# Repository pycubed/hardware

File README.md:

# Hardware ⚙
<br><br>
<br>

## [All PyCubed Resources](https://www.notion.so/maholli/All-PyCubed-Resources-8738cab0dd0743239a3cde30c6066452)
Tutorials, design resources, and more!
<br>

## Details:
- 4-layer PCB, minimum trace/spacing > 8 mils.
- Can be fabricated using standard FR4 for prototypes and Isola FR408HR for flight.
  - 50 ohm controlled impedance design spec'd for FR408HR with 11 mils external and 10.7 mils interal trace widths.
  - See [PyCubed's 2019 SmallSat Paper](https://github.com/pycubed/documentation/blob/master/PyCubed_smallsat-paper.pdf) for more discussion on the stack-up.
- Zipped, ready-to-order, gerber files can be found in the root of each revision directory. 
- NOTE: PyCubed layout has been ported from Eagle to KiCad to maintain the open-source nature of the project. Visit [http://www.kicad.org/](http://www.kicad.org/) for more details on this layout tool.
<br>

## Change Log
- [mainboard-v04 ➡ mainboard-v05](https://pycubed.org/v04-v05-Change-Log-7d80b1fb81be423a9da197f820e87538)
<br>

## Interactive Bill of Materials 🛒
- [mainboard-v01](https://pycubed.github.io/hardware/mainboard-v01)
- [mainboard-v02](https://pycubed.github.io/hardware/mainboard-v02)
- [mainboard-v04](https://pycubed.github.io/hardware/mainboard-v04)
- [mainboard-v05](https://pycubed.github.io/hardware/mainboard-v05)
<br>
<br>
<br>
<br>
<br>
<br>

## License
<br />
- Hardware in this repository is licensed under a <a rel="license" href="http://creativecommons.org/licenses/by-sa/4.0/">Creative Commons Attribution-ShareAlike 4.0 International License</a>.
- Software/firmware in this repository is licensed under MIT unless otherwise indicated.

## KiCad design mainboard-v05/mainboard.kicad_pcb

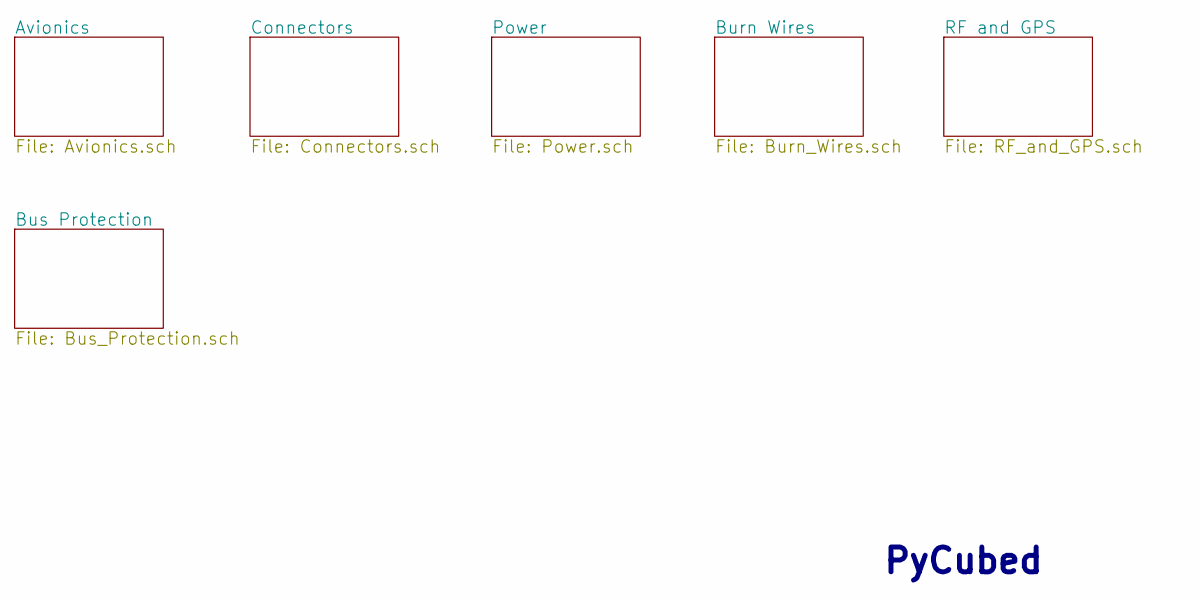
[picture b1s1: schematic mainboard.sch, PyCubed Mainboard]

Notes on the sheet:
PyCubed

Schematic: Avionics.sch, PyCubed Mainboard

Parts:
C1, C2: 8pF; C_0603_1608Metric
C3, C5, C7, C9, C10, C11: 0.1uF; C_0603_1608Metric
C4, C12, C13, C15: 1uF; C_0603_1608Metric
C14, C16: 10uF; C_0603_1608Metric
D1: WS2812B; LED_WS2812B_PLCC4_5.0x5.0mm_P3.2mm; Manufacturer_Part_Number WS2812B-B
H1, H2, H3, H4: MountingHole_Pad; MountingHole_3.2mm_M3_DIN965_Pad
J8: Conn_01x09; PinHeader_1x09_P2.54mm_Vertical
J9: Conn_01x03; PinHeader_1x03_P2.54mm_Vertical
J10: Conn_01x04; PinHeader_1x04_P2.54mm_Vertical
J15: Conn_01x02; PinHeader_CUSTOM3
L1: 10uH; L_0805_2012Metric_Pad1.15x1.40mm_HandSolder; Manufacturer_Part_Number MGFL2012F100MT-LF
R1: 316K; R_0603_1608Metric
R2: 110K; R_0603_1608Metric
R3, R4, R44, R45: 10K; R_0603_1608Metric
R6: 4.7k; R_0603_1608Metric
R7, R41, R42: 10k; R_0603_1608Metric
SW1: KMR231NG LFS; BTN_KMR2_4.6X2.8; Manufacturer_Part_Number KMR231NG LFS
U1: MAX706RESA; SO-8_3.9x4.9mm_P1.27mm; Manufacturer_Part_Number MAX706RESA
U2: ATSAMD51J19A-AU; QFP50P1200X1200X120-64N; Manufacturer_Part_Number ATSAMD51J19A-AU
U3: BMX160; Manufacturer_Part_Number BMX160
Y1: 32.768kHz; Crystal_SMD_3215-2Pin_3.2x1.5mm; Manufacturer_Part_Number SC-32S32.768kHz20PPM7pF

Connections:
3.3V: C5.1, C7.1, C9.2, C10.1, C11.1, C13.1, C15.1, C16.1, D1.1 (VDD), J8.1, J10.4, R3.1, R4.1, R44.1, R45.1, U1.2, U2.4 (PA03), U2.8 (VDDANA), U2.21 (VDDIO), U2.34 (VDDIO1), U2.48 (VDDIO2), U2.56 (VDDIO3), U3.5, U3.8, U3.12; also elsewhere on the board
/Avionics/BATTERY: C3.1, R1.2, R2.2, U2.15 (PA06)
/Avionics/XTAL1: C1.1, U2.1 (PA00), Y1.1
/Avionics/XTAL2: C2.1, U2.2 (PA01), Y1.2
AIN5: J10.2, U2.14 (PA05)
BURN_RELAY_A: U2.28 (PB15); also elsewhere on the board
DAC0: J10.1, U2.3 (PA02)
ENAB_BURN1: U2.60 (PB31); also elsewhere on the board
ENAB_BURN2: U2.32 (PA15); also elsewhere on the board
ENAB_GPS: U2.62 (PB01); also elsewhere on the board
ENAB_RF: U2.13 (PA04); also elsewhere on the board
FLASH_CS: U2.24 (PB11); also elsewhere on the board
FLASH_IO2: U2.19 (PA10); also elsewhere on the board
FLASH_IO3: U2.20 (PA11); also elsewhere on the board
FLASH_MISO: U2.18 (PA09); also elsewhere on the board
FLASH_MOSI: U2.17 (PA08); also elsewhere on the board
FLASH_SCK: U2.23 (PB10); also elsewhere on the board
GND: C1.2, C2.2, C3.2, C4.1, C5.2, C7.2, C9.1, C10.2, C11.2, C12.1, C13.2, C14.2, C15.2, C16.2, D1.3 (VSS), H1.1, H2.1, H3.1, H4.1, J8.2, J10.3, R2.1, R7.1, R41.2, SW1.B (S), SW1.B' (S1), U1.3, U1.4, U2.7 (GND), U2.22 (GND1), U2.33 (GND2), U2.47 (GND3), U2.54 (GND4), U3.2, U3.3, U3.6, U3.7; also elsewhere on the board
L1_PROG: R6.1; also elsewhere on the board
MISO: J8.5, U2.31 (PA14); also elsewhere on the board
MOSI: J8.3, U2.29 (PA12); also elsewhere on the board
unnamed: C12.2, C14.1, L1.1, U2.53 (VDDCORE)
unnamed: D1.4 (DIN), U2.42 (PA21)
unnamed: L1.2, U2.55 (VSW)
unnamed: R6.2, U2.16 (PA07)
unnamed: R41.1, U3.1
unnamed: R42.2, U1.7
unnamed: U1.1, U1.8
PA16: J15.2, U2.35 (PA16); also elsewhere on the board
PA17: J15.1, U2.36 (PA17); also elsewhere on the board
PA19: J9.3, U2.38 (PA19); also elsewhere on the board
PA20: J8.8, U2.41 (PA20); also elsewhere on the board
PA22: J8.9, U2.43 (PA22); also elsewhere on the board
PB16: J9.2, U2.39 (PB16); also elsewhere on the board
PB17: J9.1, U2.40 (PB17); also elsewhere on the board
PB22: J8.7, U2.49 (PB22); also elsewhere on the board
PB23: J8.6, U2.50 (PB23); also elsewhere on the board
RF1_CS: U2.59 (PB30); also elsewhere on the board
RF1_IO0: U2.6 (PB05); also elsewhere on the board
RF1_IO4: U2.5 (PB04); also elsewhere on the board
RF1_RST: U2.61 (PB00); also elsewhere on the board
RF2_CS: U2.12 (PB09); also elsewhere on the board
RF2_IO0: U2.9 (PB06); also elsewhere on the board
RF2_IO4: U2.10 (PB07); also elsewhere on the board
RF2_RST: U2.27 (PB14); also elsewhere on the board
RX: U2.64 (PB03); also elsewhere on the board
SCK: J8.4, U2.30 (PA13); also elsewhere on the board
SCL: R45.2, U2.26 (PB13); also elsewhere on the board
SCL_IMU: U3.13; also elsewhere on the board
SDA: R44.2, U2.25 (PB12); also elsewhere on the board
SDA_IMU: U3.14; also elsewhere on the board
SD_CS: U2.51 (PA27); also elsewhere on the board
SWCLK: R4.2, U2.57 (PA30); also elsewhere on the board
SWDIO: U2.58 (PA31); also elsewhere on the board
TX: U2.63 (PB02); also elsewhere on the board
USB_D+: U2.46 (PA25); also elsewhere on the board
USB_D-: U2.45 (PA24); also elsewhere on the board
VBATT: R1.1; also elsewhere on the board
VBUS_RESET: U2.37 (PA18); also elsewhere on the board
WDT_WDI: R7.2, U1.6, U2.44 (PA23)
~CHRG: U2.11 (PB08); also elsewhere on the board
~RESET: C4.2, R3.2, R42.1, SW1.A, SW1.A' (P1), U2.52 (RESETN); also elsewhere on the board

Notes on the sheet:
IMU
External Watch-Dog Timer
DECOUPLING
JTAG
RESET
PRIMARY PROCESSOR
Breakout Pins
Mounting Holes
Avionics
I2C ADDR
0x68
WDT enabled when installed
TCK TMS
NOTE: Components labeled "do not install" (DNI) are not populated by default
PCC D[0]-D[8]
SCL2
SDA2

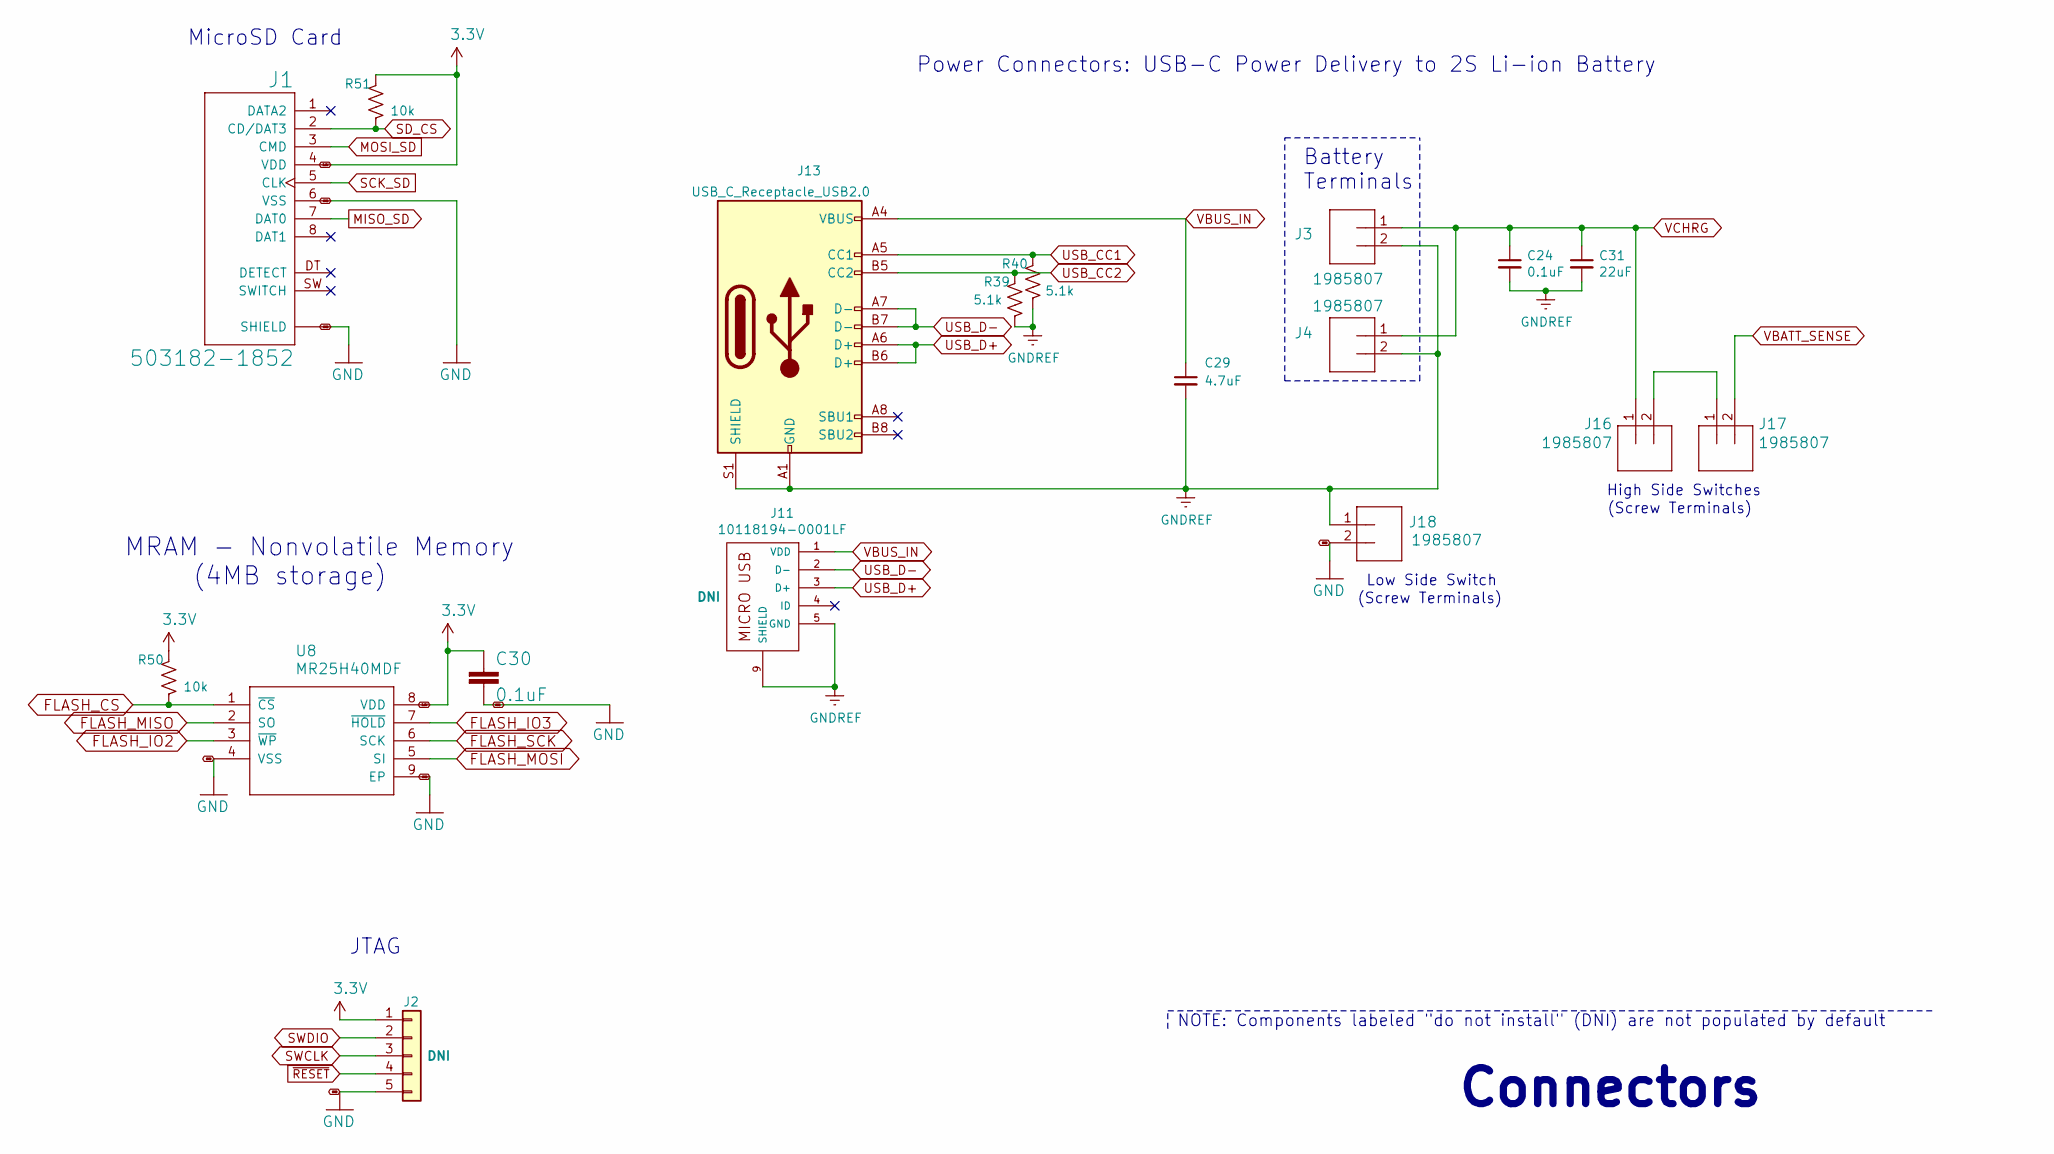
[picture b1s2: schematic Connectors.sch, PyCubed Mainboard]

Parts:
C24, C30: 0.1uF; C_0603_1608Metric
C29: 4.7uF; C_0603_1608Metric
C31: 22uF; C_0603_1608Metric
J1: 503182-1852; MOLEX_503182-1852; Manufacturer_Part_Number 5031821852
J2: Conn_01x05; PinHeader_1x05_P2.54mm_Vertical
J3, J4, J16, J17, J18: 1985807; SCREWTERMINAL-3.5MM-2_LOCK; Manufacturer_Part_Number 1985807
J11: 10118194-0001LF
J13: USB_C_Receptacle_USB2.0; USB_C_Receptacle_XKB_U262-161N-4BVC11; Manufacturer_Part_Number U262-161N-4BVC11
R39, R40: 5.1k; R_0603_1608Metric
R50, R51: 10k; R_0603_1608Metric
U8: MR25H40MDF; SON127P600X500X90-9N; Manufacturer_Part_Number W25Q80DVSNIG

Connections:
3.3V: C30.1, J1.4 (VDD), J2.1, R50.2, R51.2, U8.8 (VDD); also elsewhere on the board
FLASH_CS: R50.1, U8.1 (~CS); also elsewhere on the board
FLASH_IO2: U8.3 (~WP); also elsewhere on the board
FLASH_IO3: U8.7 (~HOLD); also elsewhere on the board
FLASH_MISO: U8.2 (SO); also elsewhere on the board
FLASH_MOSI: U8.5 (SI); also elsewhere on the board
FLASH_SCK: U8.6 (SCK); also elsewhere on the board
GND: C30.2, J1.6 (VSS), J1.P1 (SHIELD), J1.P2 (SHIELD), J1.P3 (SHIELD), J1.P4 (SHIELD), J1.P5 (SHIELD), J2.5, J18.2, U8.4 (VSS), U8.9 (EP); also elsewhere on the board
GNDREF: C24.2, C29.2, C31.2, J3.2, J4.2, J11.5 (GND), J11.8, J11.9 (SHIELD), J13.A1 (GND), J13.A12 (GND), J13.B1 (GND), J13.B12 (GND), J13.S1 (SHIELD), J18.1, R39.1, R40.1; also elsewhere on the board
MISO_SD: J1.7 (DAT0); also elsewhere on the board
MOSI_SD: J1.3 (CMD); also elsewhere on the board
unnamed: J16.2, J17.1
SCK_SD: J1.5 (CLK); also elsewhere on the board
SD_CS: J1.2 (CD/DAT3), R51.1; also elsewhere on the board
SWCLK: J2.3; also elsewhere on the board
SWDIO: J2.2; also elsewhere on the board
USB_CC1: J13.A5 (CC1), R40.2
USB_CC2: J13.B5 (CC2), R39.2
USB_D+: J11.3 (D+), J13.A6 (D+), J13.B6 (D+); also elsewhere on the board
USB_D-: J11.2 (D-), J13.A7 (D-), J13.B7 (D-); also elsewhere on the board
VBATT_SENSE: J17.2; also elsewhere on the board
VBUS_IN: C29.1, J11.1 (VDD), J13.A4 (VBUS), J13.A9 (VBUS), J13.B4 (VBUS), J13.B9 (VBUS); also elsewhere on the board
VCHRG: C24.1, C31.1, J3.1, J4.1, J16.1; also elsewhere on the board
~RESET: J2.4; also elsewhere on the board

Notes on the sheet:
High Side Switches
Battery Terminals
JTAG
Power Connectors: USB-C Power Delivery to 2S Li-ion Battery
MicroSD Card
MRAM - Nonvolatile Memory (4MB storage)
Connectors
Low Side Switch
NOTE: Components labeled "do not install" (DNI) are not populated by default
(Screw Terminals)

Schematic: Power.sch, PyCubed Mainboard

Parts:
C6, C22, C35, C39, C43: 10uF; C_0603_1608Metric
C17, C18, C28, C37, C38: 22uF; C_0603_1608Metric
C19, C20: 100uF; C_1210_3225Metric
C21, C45: 0.1uF; C_0603_1608Metric
C23: 2.2uF; C_0603_1608Metric
C25: 22nF; C_0603_1608Metric
C26, C32: 3.3nF; C_0603_1608Metric
C27, C33: 1uF; C_0603_1608Metric
C34: 4.7uF; C_0603_1608Metric
C36: 47nF; C_0603_1608Metric
D2: DFLS130L; PWRDI-123; Manufacturer_Part_Number DFLS130L-7
D5: GREEN LED; LED_0603_1608Metric; Manufacturer_Part_Number LTST-C190KGKT
J14: Conn_01x06; PinHeader_1x06_P2.54mm_Vertical
JP6, JP7: Jumper_3_Bridged12; SolderJumper-3_P1.3mm_Bridged12_RoundedPad1.0x1.5mm
L2: 3.3uH; L_2141; Manufacturer_Part_Number HPC5040NF-3R3MTH
L3: 33uH; L_1812_4532Metric; Manufacturer_Part_Number SNR5040K-330M
L4: 1uH; L_2510; Manufacturer_Part_Number MCS25GD-1R0MMP
Q1: IRLML2803; SOT-23; Manufacturer_Part_Number IRLML2803TRPbF
Q2, Q3: MBT2222ADW1T1; SOT-363_SC-70-6; Manufacturer_Part_Number MBT2222ADW1T1G
Q22: NDS8434; Manufacturer_Part_Number NDS8434
R8: 0.1; R_2512_6332Metric
R9: 107K; R_0603_1608Metric
R10: 0; R_0603_1608Metric
R11: 787K; R_0603_1608Metric
R12: 121K; R_0603_1608Metric
R13, R29: 73.2K; R_0603_1608Metric
R14: 22.1K; R_0603_1608Metric
R15, R30, R49: 100K; R_0603_1608Metric
R16: 845K; R_0603_1608Metric
R17, R18: 100k; R_0603_1608Metric
R19: 2.1M; R_0603_1608Metric
R20: 3.01K; R_0603_1608Metric
R21, R31, R46, R52, R55: 10K; R_0603_1608Metric
R22: 4.7K; R_0603_1608Metric
R23, R59: 3.3K; R_0603_1608Metric
R26: 1K; R_0603_1608Metric
R34: 5.23K; R_0603_1608Metric
R35: 30.1K; R_0603_1608Metric
R36: 3.16K; R_0603_1608Metric
R47: 200K; R_0603_1608Metric
R110: 20K; R_0603_1608Metric
U4: ADM1176-1ARMZ-R7; Manufacturer_Part_Number ADM1176-1ARMZ-R7
U5: TPS54226PWPRPWP14_2P31X2P46-L; PWP14_2P31X2P46-L; Manufacturer_Part_Number TPS54226PWPR
U6: LTC4121; QFN-16-PAD; Manufacturer_Part_Number LTC4121EUD
U7: KF50BD-TR; SOIC127P600X175-8N; Manufacturer_Part_Number KF50BD-TR
U17: BQ25883RGER; QFN50P400X400X100-25N-D; Manufacturer_Part_Number BQ25883RGER
U21: TPS7A4501DCQT; Manufacturer_Part_Number TPS7A4501DCQT

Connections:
3.3V: C17.2, C18.2, JP6.3 (B), JP7.3 (B), L2.2, Q22.1, Q22.2, Q22.3, R13.2, R17.2, R18.2, R23.1, U5.1 (VO); also elsewhere on the board
/Power/3V3_EN: Q2.6 (C1), R29.2, U5.7 (EN)
/Power/REGN: C34.1, R31.2, U17.11
/Power/VCHRG_IN: C22.1, D2.C, R10.2, R11.2, U6.P$3
/Power/V_RF: C43.2, JP6.1 (A), JP7.1 (A), R55.1, U7.1, U21.4
ENAB_GPS: R21.1, R22.1; also elsewhere on the board
ENAB_RF: U7.5, U21.1; also elsewhere on the board
GND: C17.1, C18.1, C19.2, C20.2, C22.2, C23.2, C26.2, C27.2, C28.2, C32.1, C43.1, C45.1, J14.5, Q1.2 (S), Q2.1 (E1), Q2.4 (E2), Q3.1 (E1), Q3.4 (E2), R9.2, R12.1, R14.1, R20.1, R21.2, R59.2, U4.4, U5.5 (GND), U5.8 (PGND1), U5.9 (PGND2), U5.15 (EPAD), U6.P$5, U6.P$7, U6.P$12, U6.P$17, U7.2, U7.3, U7.6, U7.7, U21.3, U21.6; also elsewhere on the board
GNDREF: C33.1, C34.2, C35.1, C37.1, C38.1, C39.1, J14.6, R35.1, R36.1, R46.1, U17.19, U17.20, U17.25; also elsewhere on the board
GPS_PWR_IN: Q22.5, Q22.6, Q22.7, Q22.8; also elsewhere on the board
L1_PROG: R20.2, U6.P$13; also elsewhere on the board
unnamed: C6.1, Q3.3 (C2), Q3.6 (C1), R49.2
unnamed: C6.2, Q2.5 (B2), R47.2
unnamed: C21.1, L2.1, U5.10 (SW1), U5.11 (SW2)
unnamed: C21.2, U5.12 (VBST)
unnamed: C23.1, U6.P$1
unnamed: C25.1, U6.P$2
unnamed: C25.2, L3.2, U6.P$4
unnamed: C26.1, U5.4 (SS)
unnamed: C27.1, R15.2, U5.3 (VREG5)
unnamed: C32.2, U4.5
unnamed: C35.2, L4.1, U17.21, U17.22
unnamed: C36.1, L4.2, U17.17, U17.18
unnamed: C36.2, U17.12
unnamed: C37.2, C38.2, J14.1, U17.15, U17.16
unnamed: C39.2, J14.3, U17.13, U17.14
unnamed: D5.2 (A), R31.1
unnamed: L3.1, U6.P$8
unnamed: Q1.1 (G), R22.2
unnamed: Q1.3 (D), Q22.4, R23.2
unnamed: Q2.2 (B1), Q2.3 (C2), R30.2, R110.2
unnamed: Q3.2 (B1), R110.1
unnamed: Q3.5 (B2), R52.1
unnamed: R9.1, R10.1, U6.P$16
unnamed: R11.1, R12.2, U6.P$6
unnamed: R13.1, R14.2, U5.2 (VFB)
unnamed: R15.1, U5.6 (PG)
unnamed: R16.1, U6.P$11
unnamed: R16.2, R19.2, U6.P$10
unnamed: R18.1, U6.P$15
unnamed: R26.2, U4.3
unnamed: R36.2, U17.8
unnamed: R55.2, R59.1, U21.5
SCL_PWR: U4.6, U17.5; also elsewhere on the board
SDA_PWR: U4.7, U17.4; also elsewhere on the board
STAT: D5.1 (K), U17.2
THM: R34.2, R35.2, R46.2, U17.7
USB_D+: U17.24; also elsewhere on the board
USB_D-: U17.1; also elsewhere on the board
VBATT: C19.1, C20.1, C28.1, C45.2, J14.2, R8.1, R19.1, R26.1, R29.1, R30.1, R47.1, R49.1, U4.2, U5.13 (VIN), U5.14 (VCC), U6.P$9, U7.8, U21.2; also elsewhere on the board
VBATT_SENSE: R8.2, U4.1; also elsewhere on the board
VBUS_IN: C33.2, R34.1, U17.23; also elsewhere on the board
VBUS_RESET: R52.2; also elsewhere on the board
VCC_RF1: JP6.2 (C); also elsewhere on the board
VCC_RF2: JP7.2 (C); also elsewhere on the board
VCHRG: J14.4; also elsewhere on the board
VSOLAR: D2.A; also elsewhere on the board
~CHRG: R17.1, U6.P$14; also elsewhere on the board

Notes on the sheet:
GPS Power
Regulator - 3.3V OUT
VBATT 4.5 to 18V
L1_PROG monitors charge current using: Ichrg=988*Vprog/Rprog 3.01K = 400mA max charge current
USB (Boost) Charging for 2-cell Li-Ion
Addr: 0x94
Power
Populating R9=107K,R10=464K sets turn-on voltage to 12V (solar input). Use this to tune efficiency
Vfloat=8.4V (2S Li-ion)
"VUSB"
VSOLAR 9V to 40V
Current Sense Resistor: 1.0 Ohm is about 0.3mW power lost as heat
NOTE: Components labeled "do not install" (DNI) are not populated by default
Input Current Limit Max input current (IINMAX)=KILIM/RILIM KILIM = 1098 to 1276 at most IINMAX=400mA=3.16 kohm
Sets EN low dwell time
"One Shot" Regulator Reset
Battery Power Monitor
"VCHRG"
"GND"
RBF Jumpers
Add jumper to allow USB battery charging (even inside P-Pod).
Add jumper to allow USB to power the board (even inside P-Pod).
Remove both jumpers before flight to remove risk of unknown BQ25883 radiation failure modes
MPPT=75% Voc R11=787K, R12=121K To disable MPTT: R11=10k; R12=DNI
MPPT on by default
2S Li-Ion Battery Solar Charging Circuit
RF Regulator
Radio VDD Select
Set RF Voltage: VOUT=1.21*(1+R55/R59)+(3E-6*R55) VOUT=5V (R55=10K, R59=3.3K)
Alternative RF Regulator B/C of 2021 Chip Shortage
LOW = enabled Opposite polarity than other RF reg..
Value is convenient, not necessary. 10K-80K would also work for R29

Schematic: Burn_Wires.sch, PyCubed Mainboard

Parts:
D4: DFLS130L; PWRDI-123; Manufacturer_Part_Number DFLS130L-7
JP8, JP9, JP10, JP11, JP12, JP13, JP14, JP15: Conn_01x03; MOLEX-1X3_LOCK; Manufacturer_Part_Number 22-23-2037
Q4: IRLML2803; SOT-23; Manufacturer_Part_Number IRLML2803TRPbF
Q5: IRLML2803; SOT-23; Manufacturer_Part_Number MMBT2222AT
Q6: MMBT2222AT; SOT-23; Manufacturer_Part_Number MMBT2222ALT1G
Q20, Q21: NDS8434; Manufacturer_Part_Number NDS8434
R25, R27, R28: 10k; R_0603_1608Metric
R32, R33: 4.7k; R_0603_1608Metric
R37, R38: 100k; R_0603_1608Metric
U16: PE014006; RELAY_PE014006; Manufacturer_Part_Number PE014006 TE

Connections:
/Burn Wires/VBURN1: JP11.3, Q20.5, Q20.6, Q20.7, Q20.8
/Burn Wires/VBURN2: JP12.3, Q21.5, Q21.6, Q21.7, Q21.8
/Burn Wires/VBURN_A_IN: Q20.1, Q20.2, Q20.3, Q21.1, Q21.2, Q21.3, R37.2, R38.2, U16.11
BURN_RELAY_A: Q6.1, R25.1; also elsewhere on the board
ENAB_BURN1: R27.1, R32.2; also elsewhere on the board
ENAB_BURN2: R28.1, R33.2; also elsewhere on the board
GND: JP8.1, JP9.1, JP10.1, JP11.1, JP12.1, JP13.1, JP14.1, JP15.1, Q4.2 (S), Q5.2 (S), Q6.2, R25.2, R27.2, R28.2, U16.12; also elsewhere on the board
unnamed: D4.A, Q6.3, U16.5 (A2)
unnamed: Q4.1 (G), R32.1
unnamed: Q5.1 (G), R33.1
unnamed: Q4.3 (D), Q20.4, R37.1
unnamed: Q5.3 (D), Q21.4, R38.1
VBATT: D4.C, U16.1 (A1), U16.14; also elsewhere on the board
VSOLAR: JP8.2, JP9.2, JP10.2, JP11.2, JP12.2, JP13.2, JP14.2, JP15.2; also elsewhere on the board

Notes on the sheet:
Power Relay A
Burn Wire Control (Antenna Depolyment)
Antenna Board Connectors
Solar Panel Connectors
Burn Wires
NOTE: Components labeled "do not install" (DNI) are not populated by default

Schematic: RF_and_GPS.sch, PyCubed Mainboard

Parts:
C44, C46: 10uF; C_0603_1608Metric
J5, J6, J7, J12: Amphenol_901-144; SMA_Amphenol_901-144_Vertical; Manufacturer_Part_Number 901-144
R5, R43: 10k; R_0603_1608Metric
R24: 10K; R_0603_1608Metric
R54, R56, R57, R58: 0; R_0805_2012Metric
U9, U10, U11, U12: XTB-40; XTB40_payload
U13: EP2W+; QFN32-5X5MM; Manufacturer_Part_Number EP2W+
U14: S1216V8; S1216_24PIN_PACKAGE
U15, U20: RFM9xBreakout; HOPERF_RFM9XW_SMD
U23: RFM98PW; RFM95PW; Manufacturer_Part_Number RFM98PW
U24: RFM98PW; RFM95PW

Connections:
3.3V: R5.1, R43.1, R54.1, R57.1, U9.9, U10.9, U11.9, U12.9, U23.9, U24.9; also elsewhere on the board
/RF and GPS/PYLD12_VDD: R54.2, R56.1, U10.11, U10.16, U12.11, U12.16
/RF and GPS/PYLD34_VDD: R57.2, R58.1, U9.11, U9.16, U11.11, U11.16
/RF and GPS/RF2_ANT: J12.1 (In), U15.9, U24.1
/RF and GPS/RF_IN: U13.4 (SUM_PORT), U14.11 (RF_IN)
GND: C44.1, C46.1, J5.2 (Ext), J6.2 (Ext), J7.2 (Ext), J12.2 (Ext), U9.8, U9.10, U9.15, U10.8, U10.10, U10.15, U11.8, U11.10, U11.15, U12.8, U12.10, U12.15, U13.1 (GND), U13.2 (GND), U13.3 (GND), U13.5 (GND), U13.6 (GND), U13.7 (GND), U13.8 (GND), U13.9 (GND), U13.10 (GND), U13.11 (GND), U13.12 (GND), U13.13 (GND), U13.14 (GND), U13.16 (GND), U13.17 (GND), U13.18 (GND), U13.19 (GND), U13.20 (GND), U13.21 (GND), U13.22 (GND), U13.23 (GND), U13.24 (GND), U13.25 (GND), U13.27 (GND), U13.28 (GND), U13.29 (GND), U13.30 (GND), U13.31 (GND), U13.32 (GND), U13.EP (GND), U14.10 (GND@10), U14.12 (GND@12), U14.13 (GND@13), U14.24 (GND@24), U15.1, U15.8, U15.10, U23.2, U23.16, U23.17, U24.2, U24.16, U24.17; also elsewhere on the board
GPS_PWR_IN: R24.2, U14.22 (V_BCKP), U14.23 (VCC); also elsewhere on the board
MISO: U9.6, U10.6, U11.6, U12.6; also elsewhere on the board
MISO_RF1: U23.10; also elsewhere on the board
MISO_RF2: U15.2, U24.10; also elsewhere on the board
MOSI: U9.4, U10.4, U11.4, U12.4; also elsewhere on the board
MOSI_RF1: U23.11; also elsewhere on the board
MOSI_RF2: U15.3, U24.11; also elsewhere on the board
unnamed: J5.1 (In), U13.15 (PORT1)
unnamed: J6.1 (In), U13.26 (PORT2)
unnamed: R24.1, U14.8 (RSTN)
PA16: U11.1, U12.23; also elsewhere on the board
PA17: U11.2, U12.22; also elsewhere on the board
PA19: U9.18, U12.7, U12.18; also elsewhere on the board
PA20: U9.7, U9.17, U10.7; also elsewhere on the board
PA22: U11.7, U12.17; also elsewhere on the board
PB16: U9.20, U12.3, U12.20; also elsewhere on the board
PB17: U9.21, U10.3; also elsewhere on the board
PB22: U11.3, U12.21; also elsewhere on the board
PB23: U9.3, U9.22, U10.2; also elsewhere on the board
RF1_ANT: J7.1 (In), U23.1
RF1_CS: R5.2, U23.13; also elsewhere on the board
RF1_IO0: U23.6; also elsewhere on the board
RF1_IO4: U23.4; also elsewhere on the board
RF1_RST: U23.14; also elsewhere on the board
RF2_CS: R43.2, U15.5, U24.13; also elsewhere on the board
RF2_IO0: U15.14, U24.6; also elsewhere on the board
RF2_IO4: U15.12, U24.4; also elsewhere on the board
RF2_RST: U15.6, U24.14; also elsewhere on the board
RX: U14.20 (TXD); also elsewhere on the board
SCK: U9.5, U10.5, U11.5, U12.5; also elsewhere on the board
SCK_RF1: U23.12; also elsewhere on the board
SCK_RF2: U15.4, U24.12; also elsewhere on the board
TX: U14.21 (RXD); also elsewhere on the board
VBATT: R56.2, R58.2; also elsewhere on the board
VCC_RF1: C44.2, U23.5; also elsewhere on the board
VCC_RF2: C46.2, U15.13, U24.5; also elsewhere on the board

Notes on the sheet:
GPS Module
RF Splitter (2 Way, 0deg DC-Pass)
Modular Radios (HopeRF format)
Radio #1
Radio, GPS, Payloads
Modular Payloads
Radio #2
NOTE: Components labeled "do not install" (DNI) are not populated by default
PAYLOAD 1
PAYLOAD 3
PAYLOAD 4
PAYLOAD 2

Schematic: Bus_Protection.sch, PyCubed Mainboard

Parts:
C8, C40, C41, C42: 10nF; C_0603_1608Metric
Q7, Q8, Q15, Q16: MBT2222ADW1T1; SOT-363_SC-70-6; Manufacturer_Part_Number MBT2222ADW1T1G
Q11: MMDT2907; SOT-363_SC-70-6; Manufacturer_Part_Number MMDT2907AQ-7-F
Q12, Q13, Q18, Q19: BSS138DWQ-7; Manufacturer_Part_Number BSS138DWQ-7
Q17: MMBT2907; SOT-23; Manufacturer_Part_Number MMBT2907ALT1G
R48, R53, R97, R98, R99, R101, R104, R107, R108, R109: 0; R_0603_1608Metric
R60, R92: 4.7k; R_0603_1608Metric
R61, R62, R66, R67, R82, R83, R84, R85: 10K; R_0603_1608Metric
R63, R64, R69, R70, R77, R78: 1K; R_0603_1608Metric
R68: 4.7K; R_0603_1608Metric
R71, R72, R86, R87: 680; R_0603_1608Metric
R73, R74, R93, R94: 100K; R_0603_1608Metric
R75, R76, R95, R96: 200K; R_0603_1608Metric

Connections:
3.3V: R61.1, R62.1, R66.1, R67.1, R73.1, R74.1, R82.1, R83.1, R84.1, R85.1, R93.1, R94.1; also elsewhere on the board
GND: C8.2, C40.2, C41.2, C42.2, Q12.1, Q12.4, Q13.1, Q13.4, Q18.1, Q18.4, Q19.1, Q19.4; also elsewhere on the board
MISO: Q11.3, Q11.6, Q17.3, R101.2, R104.2, R107.2; also elsewhere on the board
MISO_RF1: R99.2, R101.1; also elsewhere on the board
MISO_RF2: R48.2, R107.1; also elsewhere on the board
MISO_SD: R53.2, R104.1; also elsewhere on the board
MOSI: R64.2, R70.1, R77.2; also elsewhere on the board
MOSI_RF1: R70.2; also elsewhere on the board
MOSI_RF2: R77.1; also elsewhere on the board
MOSI_SD: R64.1; also elsewhere on the board
unnamed: C8.1, Q12.5, R75.2
unnamed: C40.1, Q13.5, R76.2
unnamed: C41.1, Q18.5, R95.2
unnamed: C42.1, Q19.5, R96.2
unnamed: Q7.2 (B1), R71.1
unnamed: Q8.2 (B1), R72.1
unnamed: Q11.1, R99.1
unnamed: Q11.2, R68.1
unnamed: Q11.4, R53.1
unnamed: Q11.5, R92.1
unnamed: Q12.2, Q12.3, R73.2
unnamed: Q7.5 (B2), Q12.6, R61.2, R71.2
unnamed: Q13.2, Q13.3, R74.2
unnamed: Q8.5 (B2), Q13.6, R62.2, R72.2
unnamed: Q15.2 (B1), R86.1
unnamed: Q15.5 (B2), Q18.6, R82.2, R86.2
unnamed: Q16.2 (B1), R87.1
unnamed: Q16.5 (B2), Q19.6, R83.2, R87.2
unnamed: Q17.1, R60.1
unnamed: Q17.2, R48.1
unnamed: Q18.2, Q18.3, R93.2
unnamed: Q19.2, Q19.3, R94.2
RF1_CS: R68.2; also elsewhere on the board
RF2_CS: R60.2; also elsewhere on the board
SCK: R63.2, R69.2, R78.2; also elsewhere on the board
SCK_RF1: R69.1; also elsewhere on the board
SCK_RF2: R78.1; also elsewhere on the board
SCK_SD: R63.1; also elsewhere on the board
SCL: Q7.1 (E1), Q7.3 (C2), Q15.1 (E1), Q15.3 (C2), R97.2, R108.2; also elsewhere on the board
SCL_IMU: Q7.4 (E2), Q7.6 (C1), R66.2, R75.1, R97.1; also elsewhere on the board
SCL_PWR: Q15.4 (E2), Q15.6 (C1), R84.2, R95.1, R108.1; also elsewhere on the board
SDA: Q8.1 (E1), Q8.3 (C2), Q16.1 (E1), Q16.3 (C2), R98.2, R109.2; also elsewhere on the board
SDA_IMU: Q8.4 (E2), Q8.6 (C1), R67.2, R76.1, R98.1; also elsewhere on the board
SDA_PWR: Q16.4 (E2), Q16.6 (C1), R85.2, R96.1, R109.1; also elsewhere on the board
SD_CS: R92.2; also elsewhere on the board

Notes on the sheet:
Bus Protection
NOTE: Components labeled "do not install" (DNI) are not populated by default
I2C Bus Protection - IMU
I2C Bus Protection - Power Monitor & USB Charger
SPI Bus Protection - SD Card and Payloads
SPI Bus Protection - Radio 1
SPI Bus Protection - Radio 2
Bus Protection - Bypass Jumpers
These novel bus protection circuits prevent traditional I2C/SPI failure modes where a single slave failure can disable the entire bus. Learn more: https://doi.org/10.36227/techrxiv.15166620 By default, slave clock and/or data lines can be held low and the Master (SAMD51) will still be able to commu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
NOTE

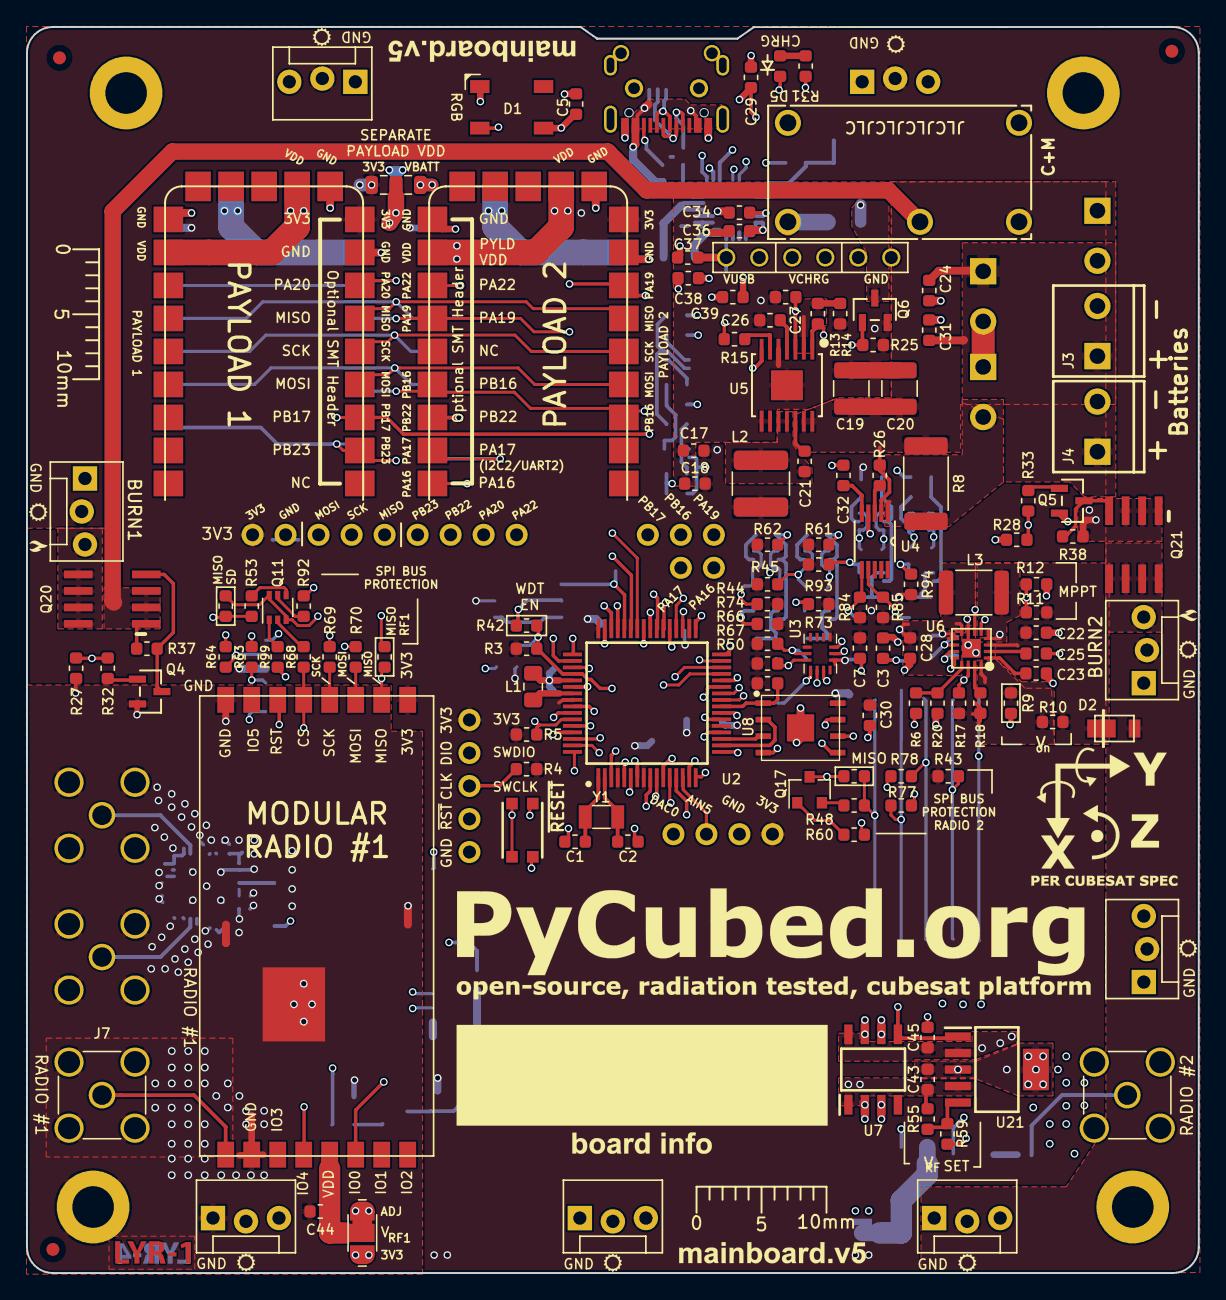
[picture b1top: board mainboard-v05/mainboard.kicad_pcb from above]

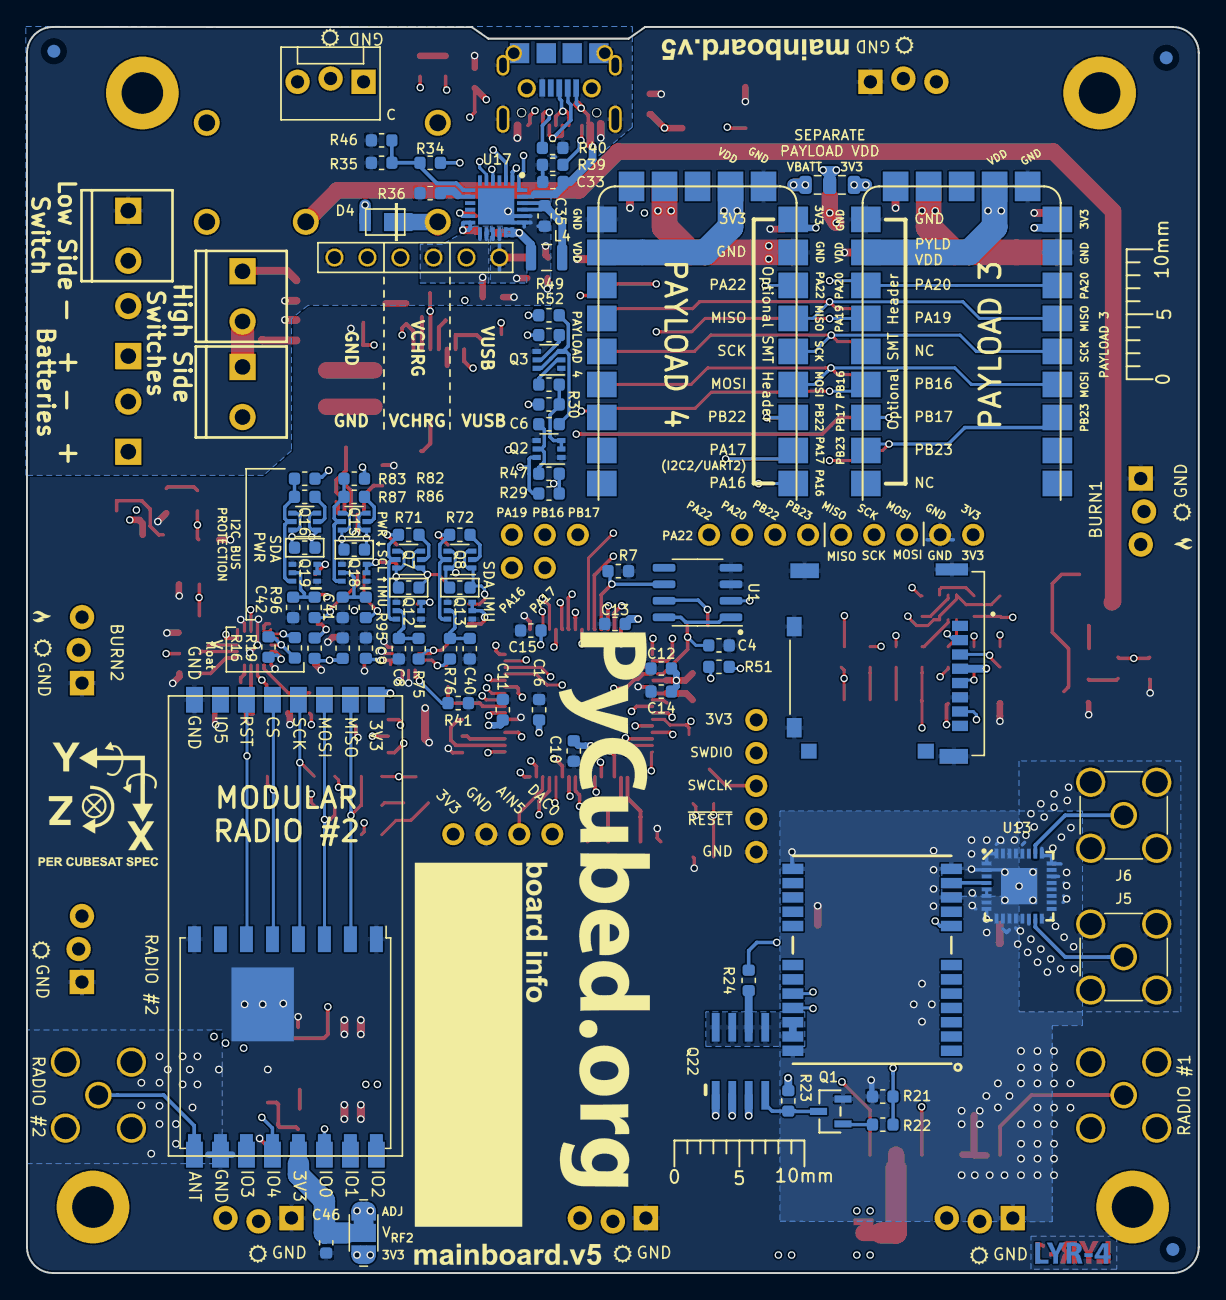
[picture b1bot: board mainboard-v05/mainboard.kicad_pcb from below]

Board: 4 copper layers, 90.2 x 95.9 mm, 230 parts (91 on the bottom side), 160 nets.

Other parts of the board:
REF1B, REF1T, REF2B, REF2T, REF3B, REF3T: Fiducial_1mm_Mask2mm

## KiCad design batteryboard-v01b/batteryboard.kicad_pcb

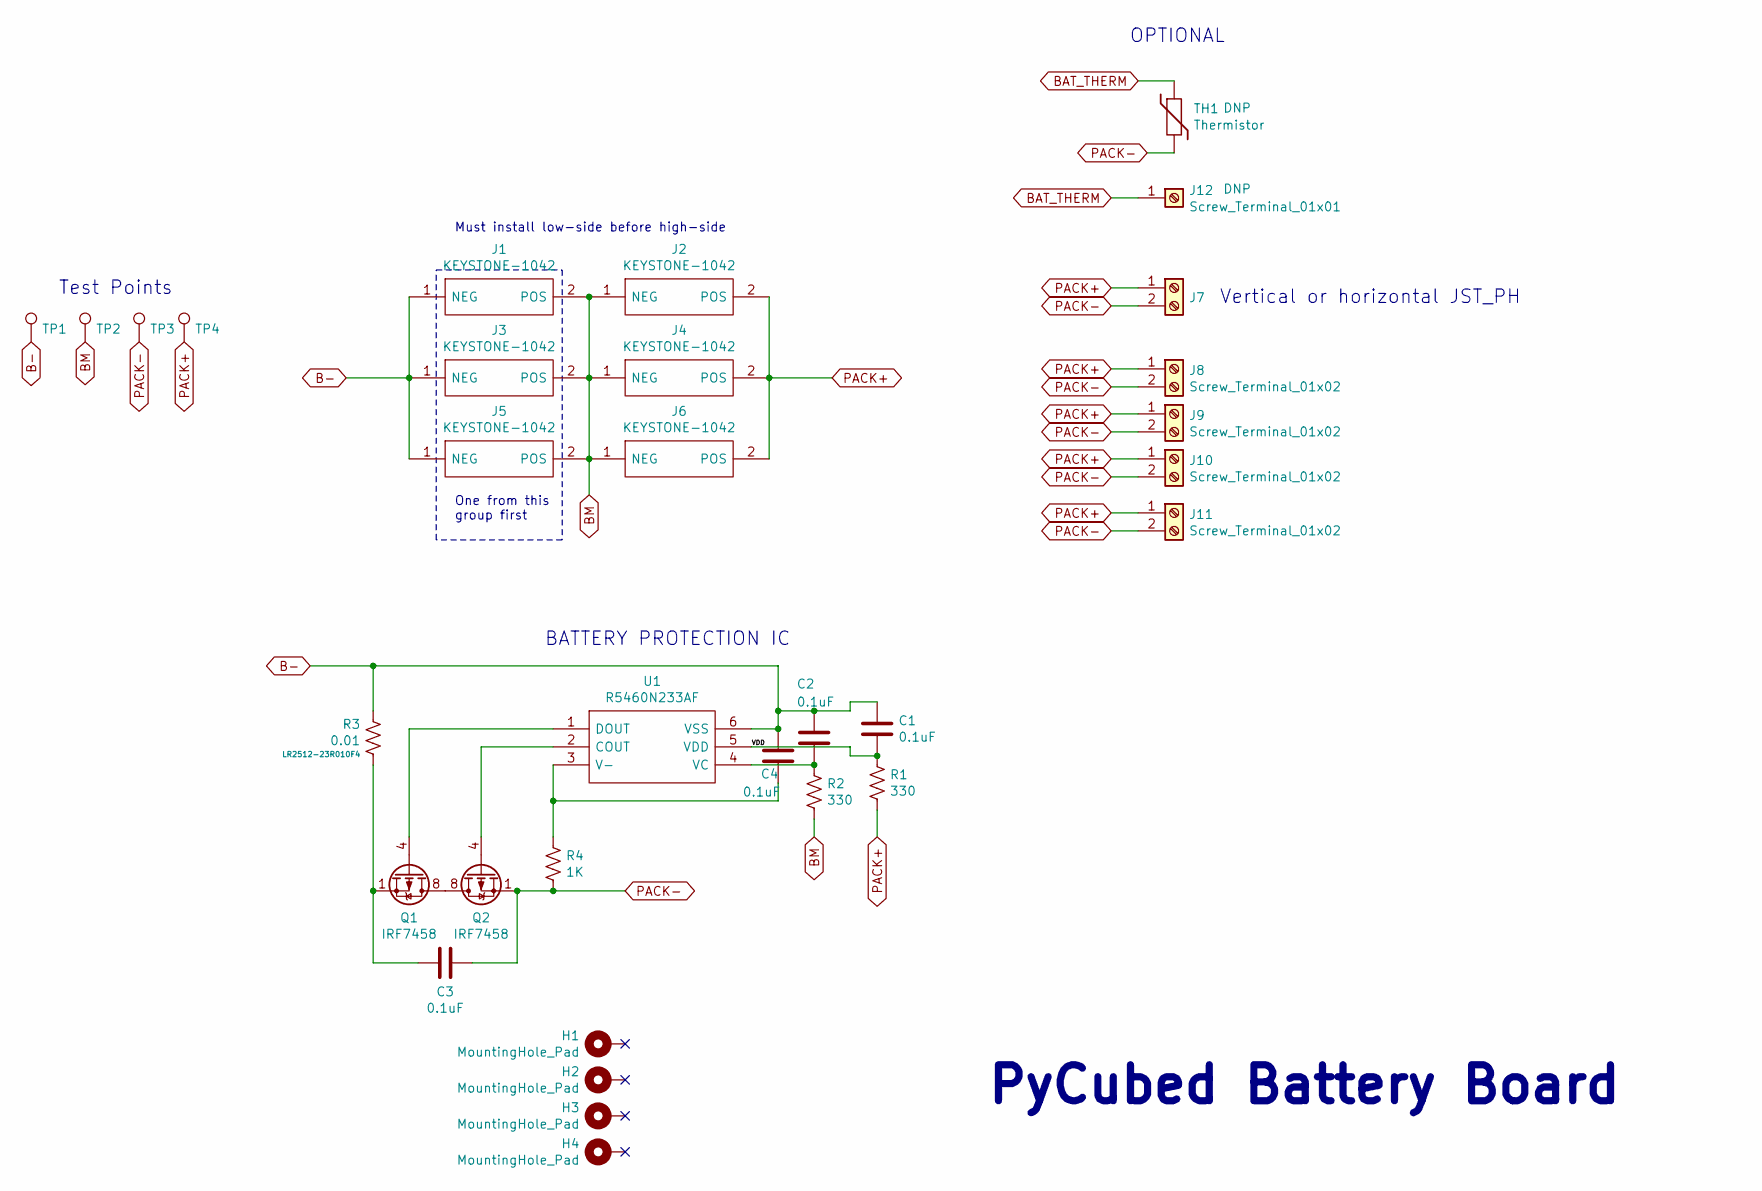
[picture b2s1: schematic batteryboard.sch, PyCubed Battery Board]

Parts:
C1, C2, C3, C4: 0.1uF; C_0603_1608Metric
H1, H2, H3, H4: MountingHole_Pad; MountingHole_3.2mm_M3_DIN965_PadMOD
J1, J2, J3, J4, J5, J6: KEYSTONE-1042; Manufacturer_Part_Number 1042; Mouser Part Number 534-1042
J7: JST_PH_S2B-PH-SM4; JST_PH_S2B-PH-SM4-TB_1x02-1MP_P2.00mm_Horizontal
J8, J9, J10, J11: Screw_Terminal_01x02; SCREWTERMINAL-3.5MM-2_LOCK
J12: Screw_Terminal_01x01; PinHeader_1x01_P1.00mm_Vertical
Q1, Q2: IRF7458; SOIC-8_3.9x4.9mm_P1.27mm
R1, R2: 330; R_0603_1608Metric
R3: 0.01; R_2512_6332Metric
R4: 1K; R_0603_1608Metric; Manufacturer_Part_Number LR2512-23R010F4
TH1: Thermistor; R_Axial_DIN0204_L3.6mm_D1.6mm_P5.08mm_Vertical
TP1, TP2, TP3, TP4: TestPoint; TestPoint_Loop_D1.80mm_Drill1.0mm_Beaded
U1: R5460N233AF; SOT95P280X130-6N; Manufacturer_Part_Number R5460N233AF-TR-FE; Mouser Part Number 848-R5460N233AFTRFE

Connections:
/VDD: C1.2, R1.2, U1.5 (VDD)
B-: C1.1, C2.1, C4.1, J1.1 (NEG), J3.1 (NEG), J5.1 (NEG), R3.1, TP1.1, U1.6 (VSS)
BAT_THERM: J12.1, TH1.1
BM: J1.2 (POS), J2.1 (NEG), J3.2 (POS), J4.1 (NEG), J5.2 (POS), J6.1 (NEG), R2.1, TP2.1
unnamed: C2.2, R2.2, U1.4 (VC)
unnamed: C3.1, Q1.1 (S), Q1.2 (S), Q1.3 (S), R3.2
unnamed: C4.2, R4.1, U1.3 (V-)
unnamed: Q1.4 (G), U1.1 (DOUT)
unnamed: Q1.5 (D), Q1.6 (D), Q1.7 (D), Q1.8 (D), Q2.5 (D), Q2.6 (D), Q2.7 (D), Q2.8 (D)
unnamed: Q2.4 (G), U1.2 (COUT)
PACK+: J2.2 (POS), J4.2 (POS), J6.2 (POS), J7.1, J8.1, J9.1, J10.1, J11.1, R1.1, TP4.1
PACK-: C3.2, J7.2, J8.2, J9.2, J10.2, J11.2, Q2.1 (S), Q2.2 (S), Q2.3 (S), R4.2, TH1.2, TP3.1

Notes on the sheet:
Must install low-side before high-side
One from this group first
OPTIONAL
Test Points
Vertical or horizontal JST_PH
BATTERY PROTECTION IC
PyCubed Battery Board

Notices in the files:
parts and their libraries:
Copyright 2016 Accelerated Designs. All rights reserved.
